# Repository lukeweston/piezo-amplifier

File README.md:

3-channel piezoelectric nanopositioning amplifier

Adapted from the design of Hwu et al, with a few small changes.

https://www.sciencedirect.com/science/article/pii/S2468067222000621#f0085

Changed to a commercially manufactured 2-layer PCB, as 2-layer professional PCBs are incredibly cheap and easily available today.
Made the PCB a little more compact.

Changed power amplifier ICs to LM1875 as they are more readily available.
Heatsinks need to be screwed onto the LM1875 amplifier tabs.

Changed to SMA connectors directly on the board, to more easily connect the outputs directly to the board.

Avoiding SMD components as much as possible, as science students (who aren't electronics specialists) often struggle with them.

PCB is 100mm x 80mm, 2 layers. Standard, cheap design rules like 6 thou / 6 thou will work fine.

The Zip file in this repo contains a standard, fabrication-ready set of Gerber files for a fab such as OSHPark or PCBWay.

Board and schematic (.brd / .sch files) are in Autodesk Eagle format.

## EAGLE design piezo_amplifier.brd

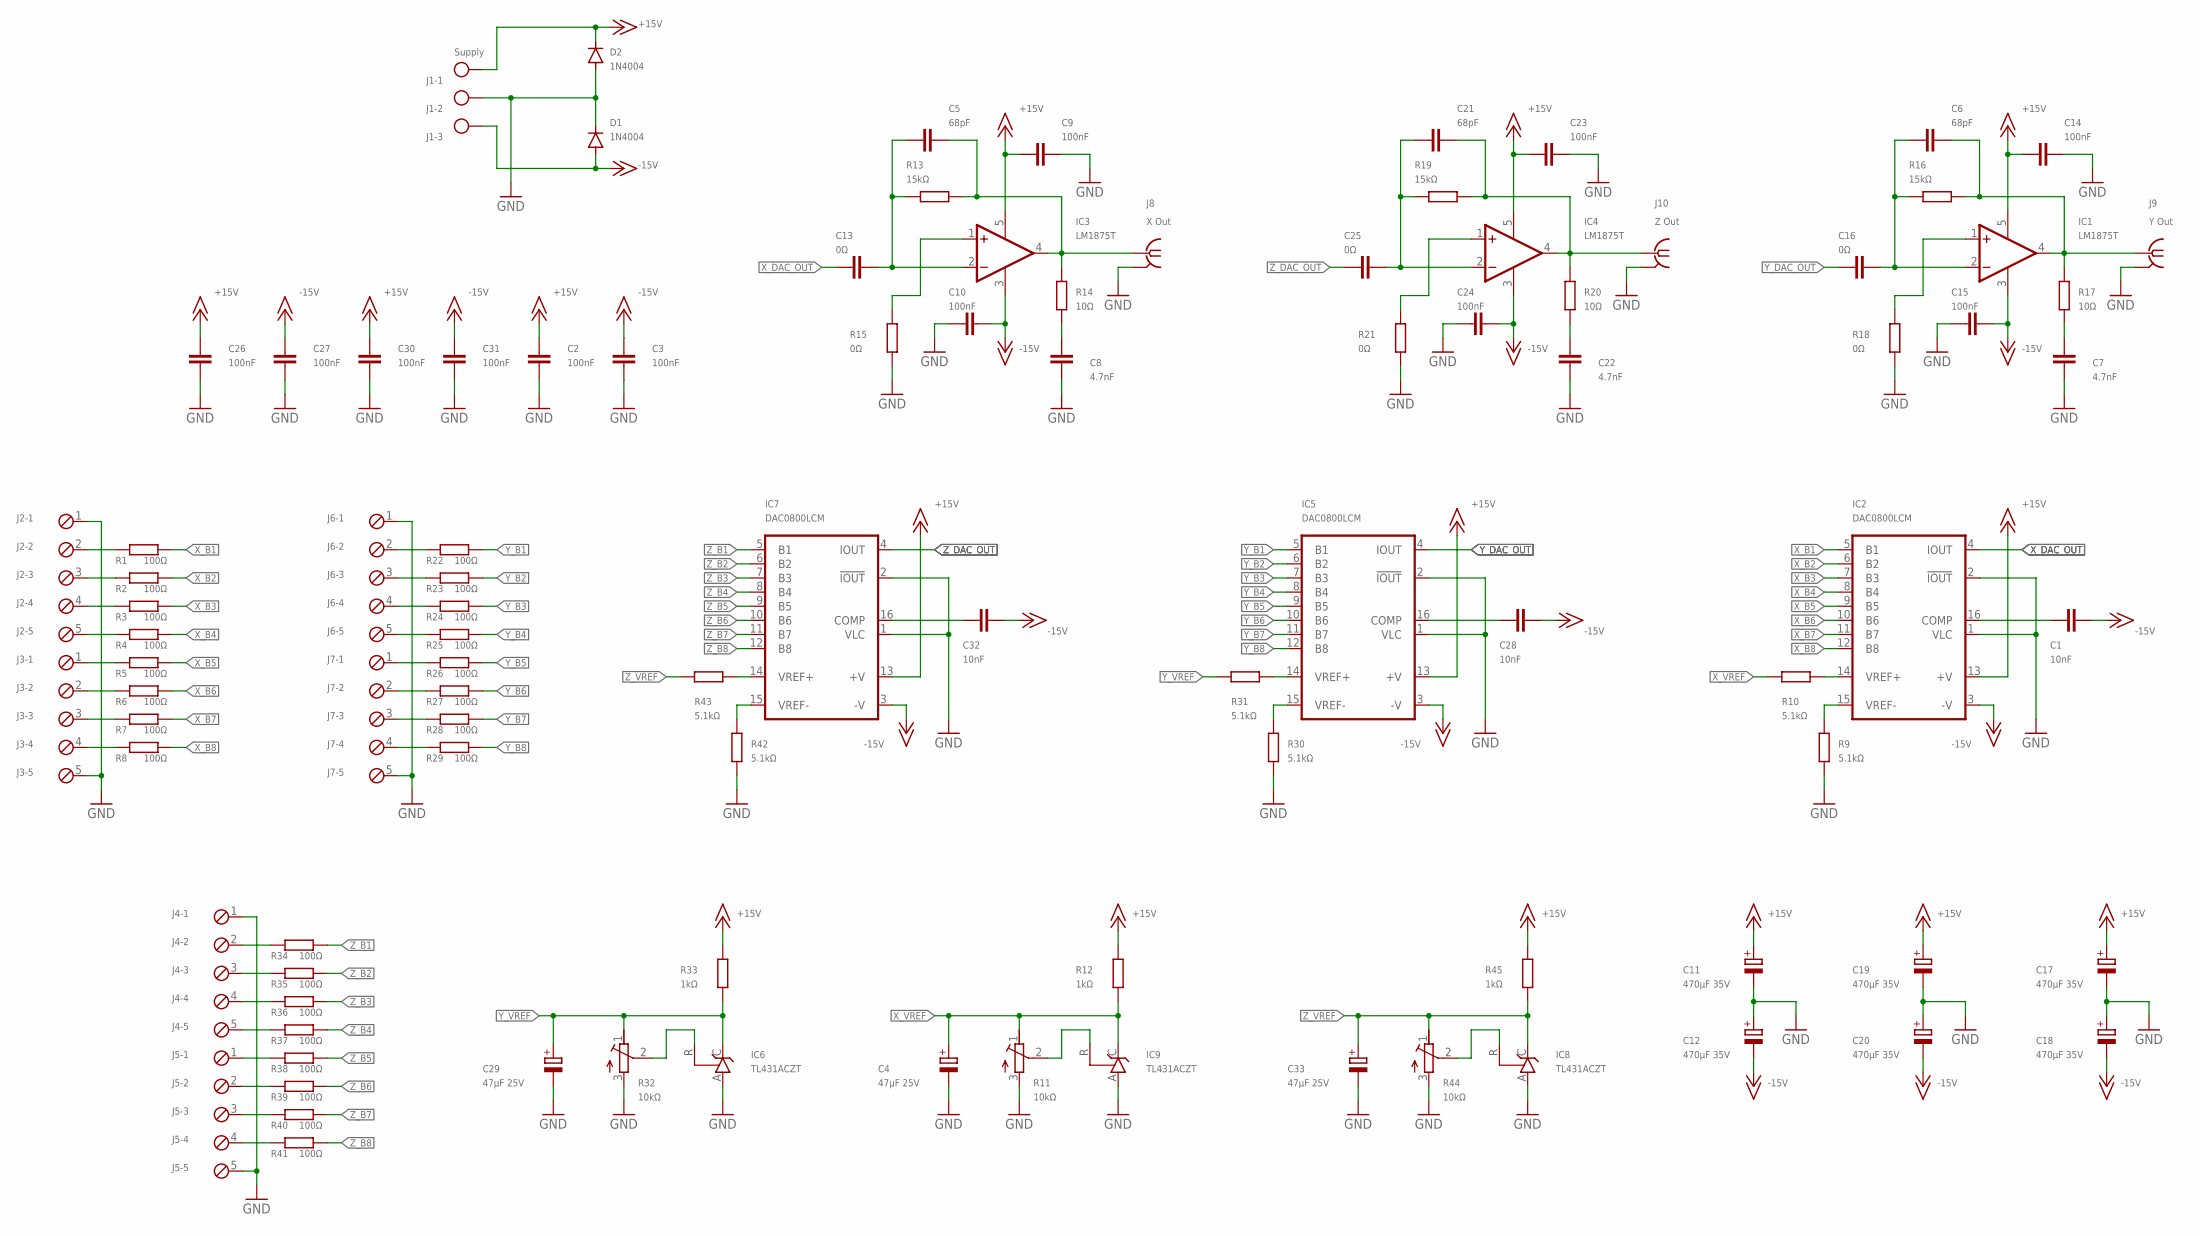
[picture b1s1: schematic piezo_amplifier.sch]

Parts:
C1, C28, C32: 10nF; C050-025X075
C2, C3, C9, C10, C14, C15, C23, C24, C26, C27, C30, C31: 100nF; C050-025X075
C4, C29, C33: 47µF 25V; E2,5-5
C5, C6, C21: 68pF; C050-025X075
C7, C8, C22: 4.7nF; C050-025X075
C11, C12, C17, C18, C19, C20: 470µF 35V; E5-8,5
C13, C16, C25: 0Ω; C050-025X075
D1, D2: 1N4004; DO41-10
IC1, IC3, IC4: LM1875T; CB367
IC2, IC5, IC7: DAC0800LCM; SO16
IC6, IC8, IC9: TL431ACZT; TO92-CLP
J1: Supply; MKDSN1,5/3-5,08
J2, J3, J4, J5, J6, J7: MPT5; 5POL254
J8: X Out; BU-SMA-V
J9: Y Out; BU-SMA-V
J10: Z Out; BU-SMA-V
R1, R2, R3, R4, R5, R6, R7, R8, R22, R23, R24, R25, R26, R27, R28, R29, R34, R35, R36, R37, R38, R39, R40, R41: 100Ω; 0207/10
R9, R10, R30, R31, R42, R43: 5.1kΩ; 0207/10
R11, R32, R44: 10kΩ; RTRIMT93YA
R12, R33, R45: 1kΩ; 0207/10
R13, R16, R19: 15kΩ; 0207/10
R14, R17, R20: 10Ω; 0207/10
R15, R18, R21: 0Ω; 0207/10

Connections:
+15V: C2.2, C9.1, C11.+, C14.1, C17.+, C19.+, C23.1, C26.2, C30.2, D2.C, IC1.5 (V+), IC2.13 (+V), IC3.5 (V+), IC4.5 (V+), IC5.13 (+V), IC7.13 (+V), J1.1, R12.2, R33.2, R45.2
-15V: C1.2, C3.2, C10.2, C12.-, C15.2, C18.-, C20.-, C24.2, C27.2, C28.2, C31.2, C32.2, D1.A, IC1.3 (V-), IC2.3 (-V), IC3.3 (V-), IC4.3 (V-), IC5.3 (-V), IC7.3 (-V), J1.3
FOO: C6.2, C16.1, IC1.2 (-IN), R16.2
FOO1: C21.2, C25.1, IC4.2 (-IN), R19.2
FOO2: C5.2, C13.1, IC3.2 (-IN), R13.2
GND: C2.1, C3.1, C4.-, C7.2, C8.2, C9.2, C10.1, C11.-, C12.+, C14.2, C15.1, C17.-, C18.+, C19.-, C20.+, C22.2, C23.2, C24.1, C26.1, C27.1, C29.-, C30.1, C31.1, C33.-, D1.C, D2.A, IC2.1 (VLC), IC2.2 (!IOUT), IC5.1 (VLC), IC5.2 (!IOUT), IC6.A, IC7.1 (VLC), IC7.2 (!IOUT), IC8.A, IC9.A, J1.2, J2.1, J3.5, J4.1, J5.5, J6.1, J7.5, J8.2, J8.3 (2), J8.4 (2), J8.5 (2), J9.2, J9.3 (2), J9.4 (2), J9.5 (2), J10.2, J10.3 (2), J10.4 (2), J10.5 (2), R9.1, R11.3 (A), R15.2, R18.2, R21.2, R30.1, R32.3 (A), R42.1, R44.3 (A)
unnamed: IC9.R, R11.2 (S)
unnamed: C5.1, IC3.4 (OUT), J8.1, R13.1, R14.2
unnamed: C6.1, IC1.4 (OUT), J9.1, R16.1, R17.2
unnamed: C8.1, R14.1
unnamed: IC3.1 (+IN), R15.1
unnamed: C7.1, R17.1
unnamed: IC1.1 (+IN), R18.1
unnamed: C21.1, IC4.4 (OUT), J10.1, R19.1, R20.2
unnamed: J2.3, R2.1
unnamed: J2.2, R1.1
unnamed: J2.4, R3.1
unnamed: J2.5, R4.1
unnamed: J3.1, R5.1
unnamed: J3.2, R6.1
unnamed: J3.3, R7.1
unnamed: J3.4, R8.1
unnamed: C22.1, R20.1
unnamed: IC4.1 (+IN), R21.1
unnamed: J6.2, R22.1
unnamed: J6.3, R23.1
unnamed: J6.4, R24.1
unnamed: J6.5, R25.1
unnamed: J7.1, R26.1
unnamed: J7.2, R27.1
unnamed: C1.1, IC2.16 (COMP)
unnamed: J7.3, R28.1
unnamed: J7.4, R29.1
unnamed: IC2.14 (VREF+), R10.1
unnamed: IC2.15 (VREF-), R9.2
unnamed: C28.1, IC5.16 (COMP)
unnamed: IC5.14 (VREF+), R31.1
unnamed: IC5.15 (VREF-), R30.2
unnamed: IC6.R, R32.2 (S)
unnamed: J4.2, R34.1
unnamed: J4.3, R35.1
unnamed: J4.4, R36.1
unnamed: J4.5, R37.1
unnamed: J5.1, R38.1
unnamed: J5.2, R39.1
unnamed: J5.3, R40.1
unnamed: J5.4, R41.1
unnamed: C32.1, IC7.16 (COMP)
unnamed: IC7.14 (VREF+), R43.1
unnamed: IC7.15 (VREF-), R42.2
unnamed: IC8.R, R44.2 (S)
X_B1: IC2.5 (B1), R1.2
X_B2: IC2.6 (B2), R2.2
X_B3: IC2.7 (B3), R3.2
X_B4: IC2.8 (B4), R4.2
X_B5: IC2.9 (B5), R5.2
X_B6: IC2.10 (B6), R6.2
X_B7: IC2.11 (B7), R7.2
X_B8: IC2.12 (B8), R8.2
X_DAC_OUT: C13.2, IC2.4 (IOUT)
X_VREF: C4.+, IC9.C, R10.2, R11.1 (E), R12.1
Y_B1: IC5.5 (B1), R22.2
Y_B2: IC5.6 (B2), R23.2
Y_B3: IC5.7 (B3), R24.2
Y_B4: IC5.8 (B4), R25.2
Y_B5: IC5.9 (B5), R26.2
Y_B6: IC5.10 (B6), R27.2
Y_B7: IC5.11 (B7), R28.2
Y_B8: IC5.12 (B8), R29.2
Y_DAC_OUT: C16.2, IC5.4 (IOUT)
Y_VREF: C29.+, IC6.C, R31.2, R32.1 (E), R33.1
Z_B1: IC7.5 (B1), R34.2
Z_B2: IC7.6 (B2), R35.2
Z_B3: IC7.7 (B3), R36.2
Z_B4: IC7.8 (B4), R37.2
Z_B5: IC7.9 (B5), R38.2
Z_B6: IC7.10 (B6), R39.2
Z_B7: IC7.11 (B7), R40.2
Z_B8: IC7.12 (B8), R41.2
Z_DAC_OUT: C25.2, IC7.4 (IOUT)
Z_VREF: C33.+, IC8.C, R43.2, R44.1 (E), R45.1

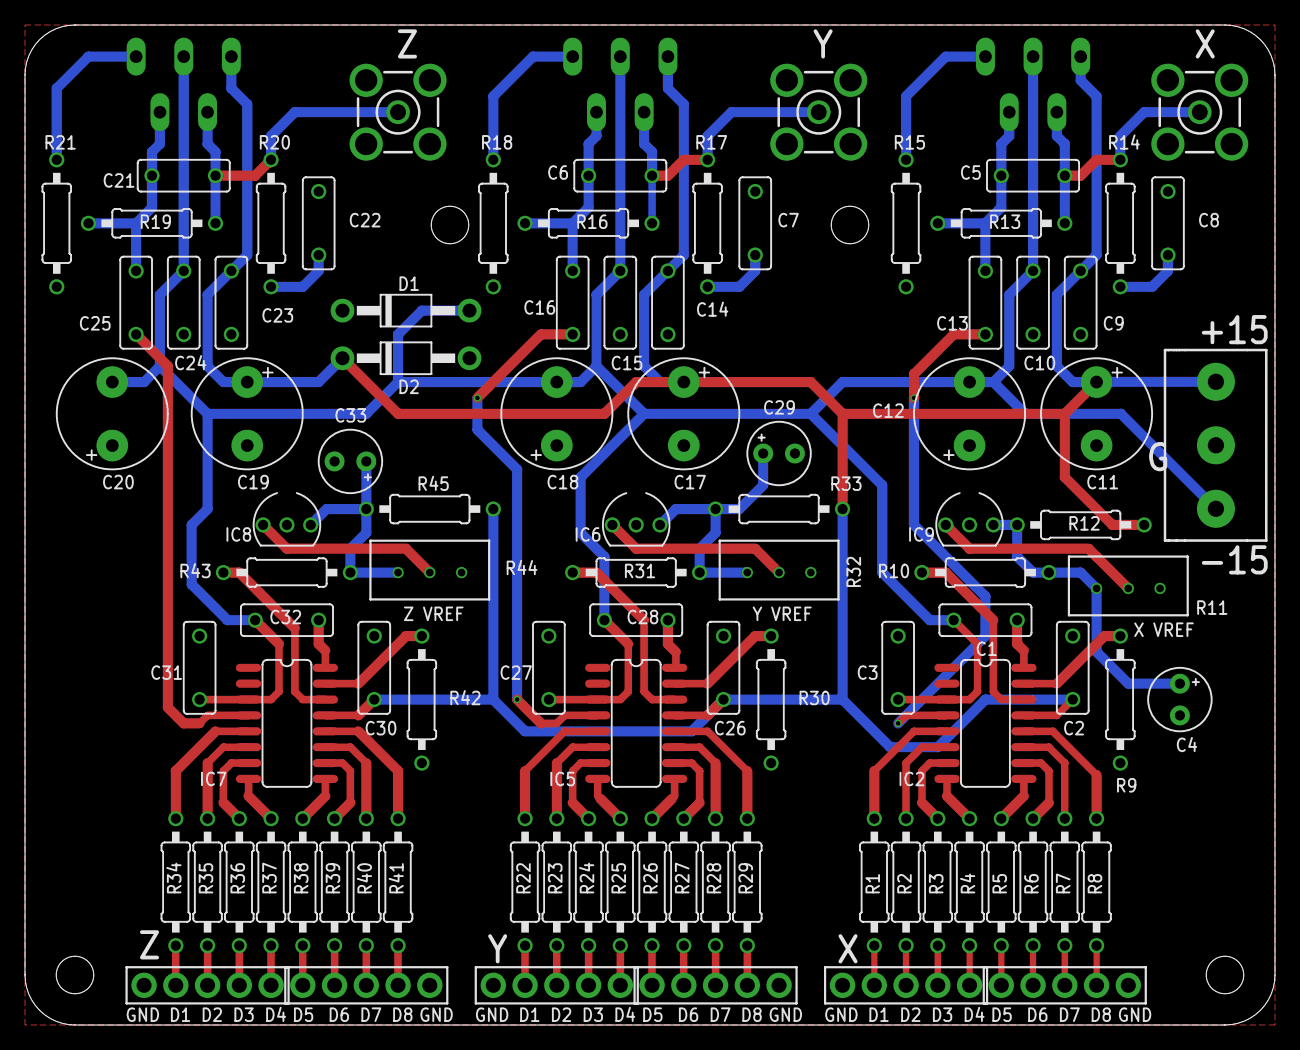
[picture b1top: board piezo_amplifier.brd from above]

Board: 2 copper layers, 100.0 x 80.0 mm, 99 parts (0 on the bottom side), 81 nets.
